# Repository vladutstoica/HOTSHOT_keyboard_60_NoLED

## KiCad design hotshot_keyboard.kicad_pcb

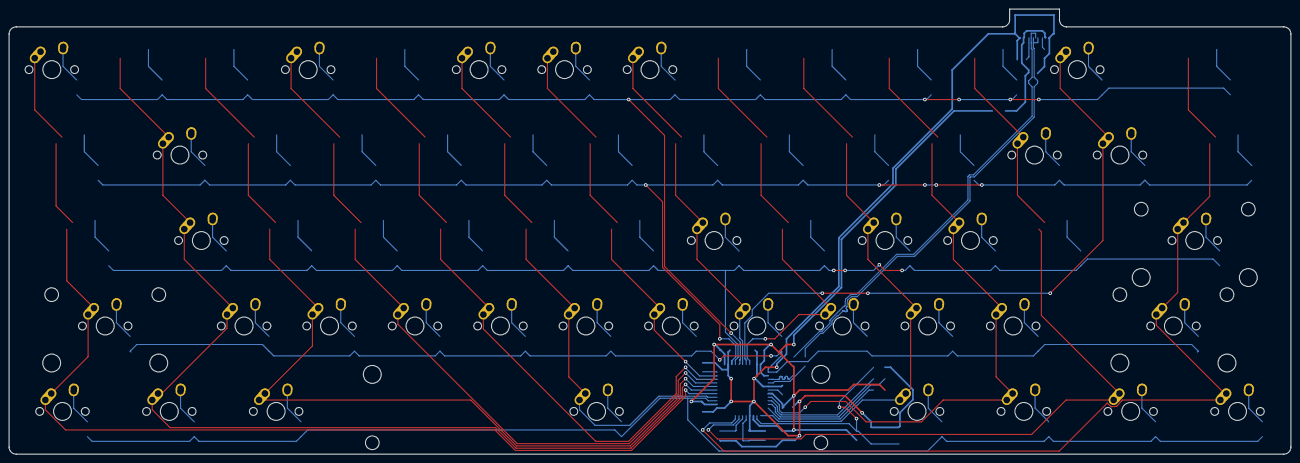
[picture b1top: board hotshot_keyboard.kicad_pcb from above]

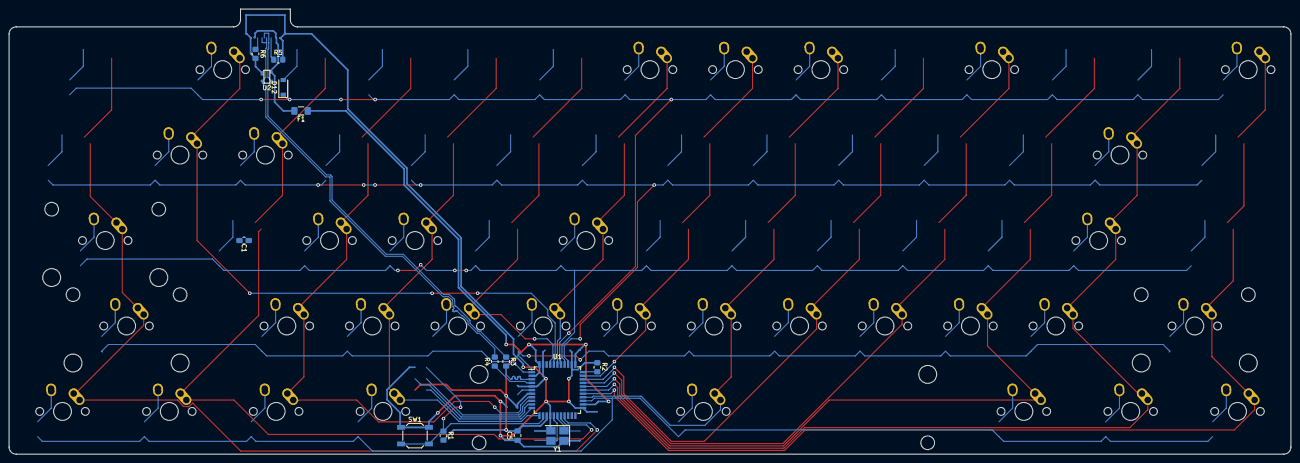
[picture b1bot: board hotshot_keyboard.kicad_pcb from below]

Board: 2 copper layers, 285.8 x 99.2 mm, 48 parts (13 on the bottom side), 26 nets.

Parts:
C5: 0.1u; C_0805_2012Metric_Pad1.18x1.45mm_HandSolder
D12: 1N4148; D_SOD-123
F1: 500mA; Fuse_1206_3216Metric_Pad1.42x1.75mm_HandSolder
MX1: ESC; MX-1U-NoLED
MX4: #3; MX-1U-NoLED
MX6: #5; MX-1U-NoLED
MX7: #6; MX-1U-NoLED
MX8: #7; MX-1U-NoLED
MX13: =+; MX-1U-NoLED
MX16: Q; MX-1U-NoLED
MX26: [{; MX-1U-NoLED
MX27: ]}; MX-1U-NoLED
MX30: A; MX-1U-NoLED
MX36: J; MX-1U-NoLED
MX38: L; MX-1U-NoLED
MX39: ;:; MX-1U-NoLED
MX40: '; MX-1U-NoLED
MX41: ENTER; MX-2.25U-NoLED
MX42: LSHIFT; MX-2.25U-NoLED
MX43: Z; MX-1U-NoLED
MX44: X; MX-1U-NoLED
MX45: C; MX-1U-NoLED
MX46: V; MX-1U-NoLED
MX47: B; MX-1U-NoLED
MX48: N; MX-1U-NoLED
MX49: M; MX-1U-NoLED
MX50: ,<; MX-1U-NoLED
MX51: .>; MX-1U-NoLED
MX52: /?; MX-1U-NoLED
MX53: RSHIFT; MX-2.75U-NoLED
MX54: LCTRL; MX-1.25U-NoLED
MX55: LCMD; MX-1.25U-NoLED
MX56: LALT; MX-1.25U-NoLED
MX57: SPACE; MX-6.25U-ReversedStabilizers-NoLED
MX58: RALT; MX-1.25U-NoLED
MX59: RCMD; MX-1.25U-NoLED
MX60: FN; MX-1.25U-NoLED
MX61: RCTRL; MX-1.25U-NoLED
R1, R2: 10k; R_0805_2012Metric_Pad1.20x1.40mm_HandSolder
R3, R4: 22; R_0805_2012Metric_Pad1.20x1.40mm_HandSolder
R5: 5.1K; R_0805_2012Metric_Pad1.20x1.40mm_HandSolder
R6: 5.1k; R_0805_2012Metric_Pad1.20x1.40mm_HandSolder
SW1: SW_Push; SW_SPST_SKQG_WithStem
U1: ATmega32U4-AU; TQFP-44_10x10mm_P0.8mm
U2: PRTR5V0U2X; SOT143B
Y1: XTAL; Crystal_SMD_3225-4Pin_3.2x2.5mm_HandSoldering

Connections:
+5V: C5.1, F1.1, R1.2, U1.2, U1.7, U1.14, U1.24, U1.34, U1.44
/COL0: MX1.1, MX42.1, MX54.1, U1.27
/COL1: MX16.1, MX30.1, MX43.1, MX55.1, U1.28
/COL2: MX44.1, MX56.1, U1.29
/COL3: MX4.1, MX45.1, U1.30
/COL4: MX46.1, U1.31
/COL5: MX6.1, MX47.1, MX57.1, U1.26
/COL6: MX7.1, MX48.1, U1.32
/COL7: MX8.1, MX36.1, MX49.1, U1.39
/COL8: MX50.1, U1.41
/COL9: MX38.1, MX51.1, MX58.1, U1.12
/COL10: MX39.1, MX52.1, MX59.1, U1.8
/COL11: MX26.1, MX60.1, U1.18
/COL12: MX13.1, MX27.1, U1.40
/COL13: MX41.1, MX53.1, MX61.1, U1.19
/D+: R4.1, U1.4
/D-: R3.1, U1.3
/DD+: R4.2, U2.2
/DD-: R3.2, U2.3
/RESET: R1.1, SW1.2, U1.13
/ROW0: D12.1, U1.38
/XTAL1: MX40.1, U1.17, Y1.1
/XTAL2: U1.16, Y1.3
GND: C5.2, MX40.2, R2.2, R5.2, R6.2, SW1.1, U1.5, U1.15, U1.23, U1.35, U1.43, U2.1, Y1.2, Y1.4
unnamed: R2.1, U1.33
VCC: F1.2, U2.4

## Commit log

2021-03-09 Add footprint libraries
2021-03-09 final schematics
2021-03-09 pcb progress
2021-03-11 update schematics
2021-03-11 update matrix
2021-03-12 update pcb
2021-03-13 update pcb zones
2021-03-14 reconfig schematics row/cols
2021-03-14 update pcb route
2021-03-15 remastered pcb
2021-03-16 update left part
2021-03-16 pcb full connected
2021-03-16 update diode
2021-03-21 update structure
2021-03-21 redo
2021-03-21 update modules
2021-03-21 update gitmodules
2021-03-21 update submodules
2021-03-25 update 3D render
2021-03-25 add copper GND to mc crystal
2021-03-29 new switch 3d file
2021-03-29 3d update
2021-03-29 update close to final file
2021-04-01 Update hotshot_keyboard.kicad_pcb-bak
2021-04-01 remove mx 3d files
2021-04-01 add .gitattributes
2021-04-01 add large blend files
2021-04-01 Add blender files 100mb+
2021-04-01 update blend files
2021-04-01 update keyboard plate
2021-04-02 new datasheets
2021-04-02 update blender files
